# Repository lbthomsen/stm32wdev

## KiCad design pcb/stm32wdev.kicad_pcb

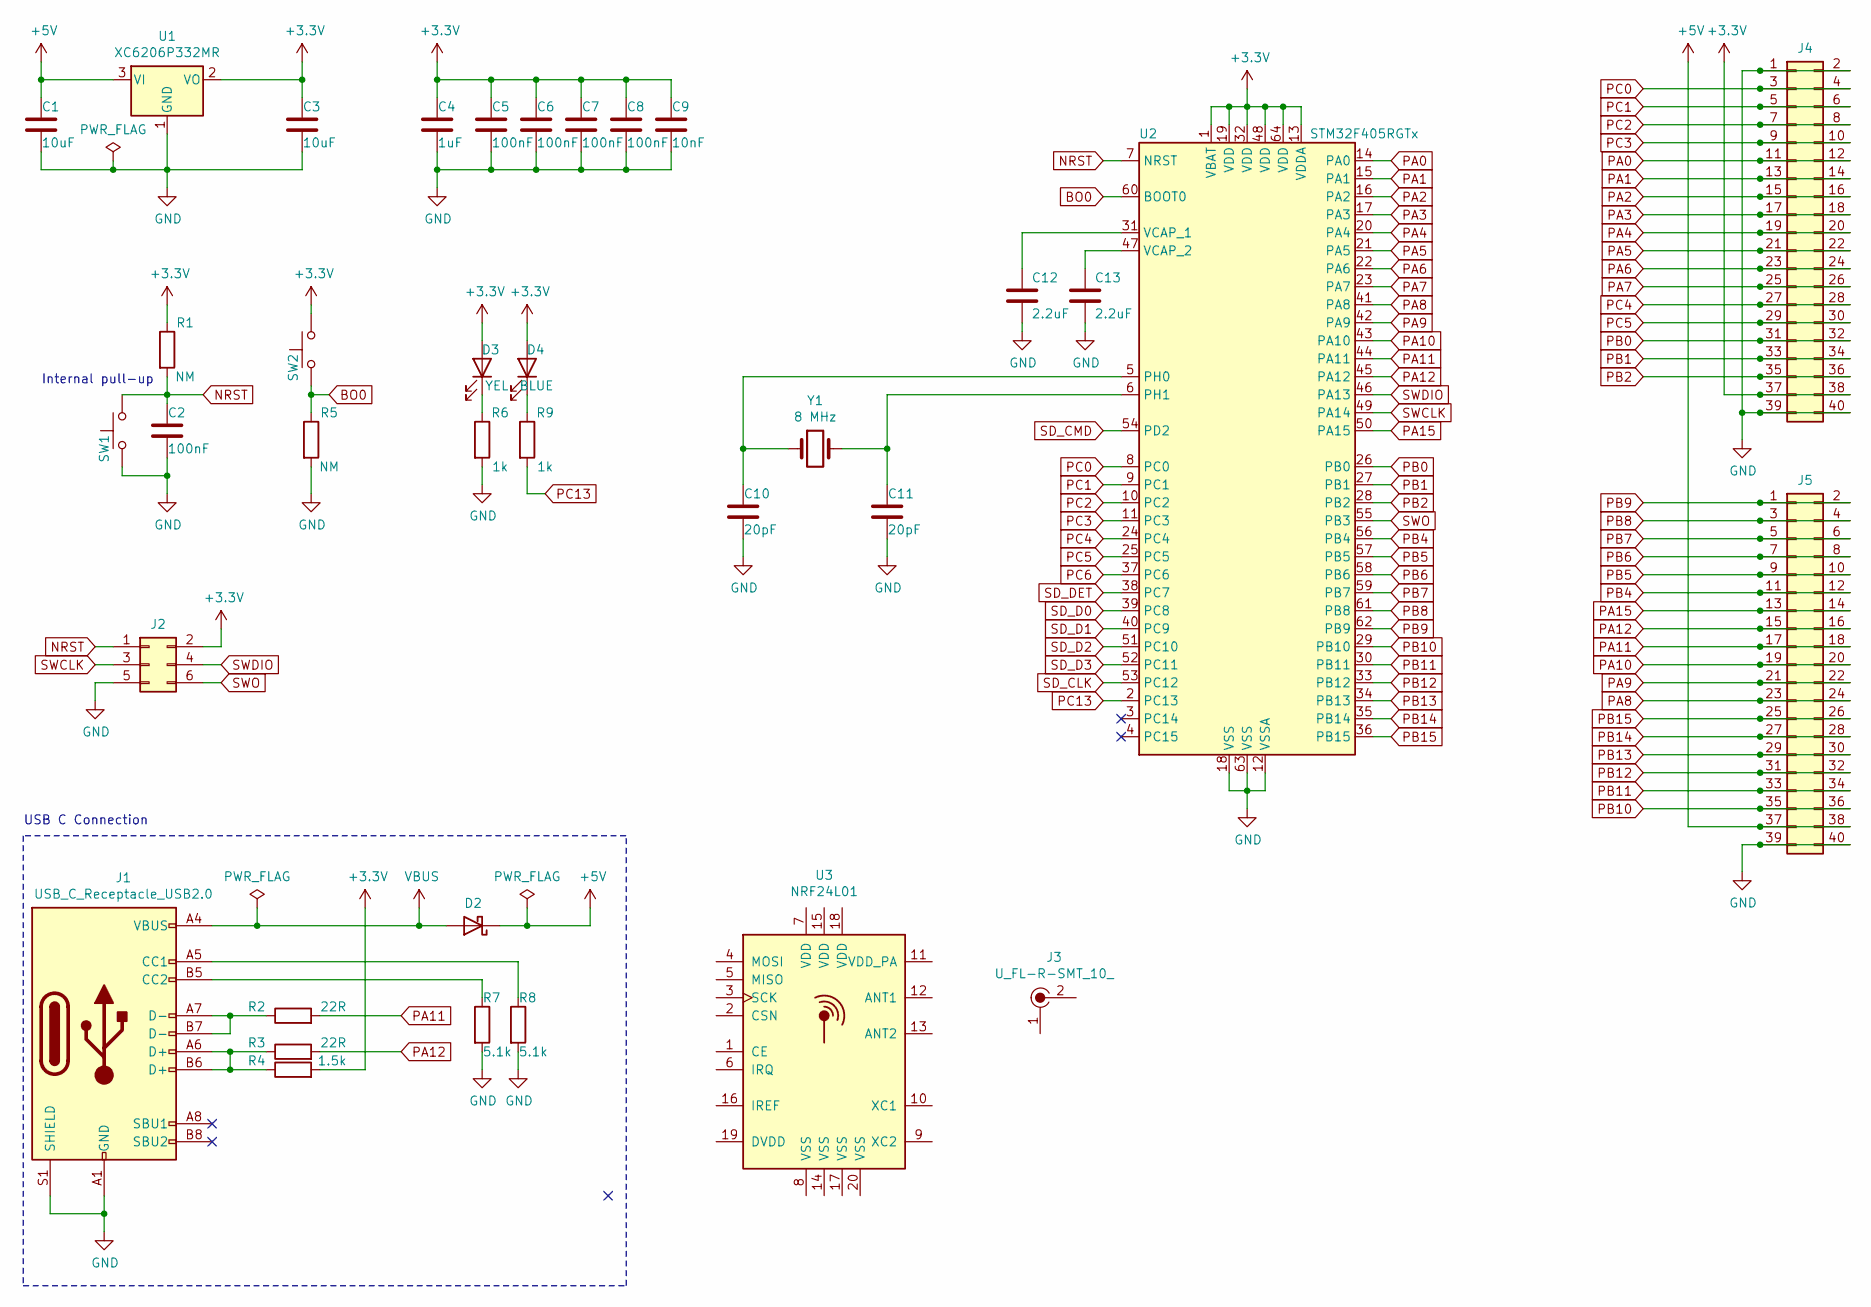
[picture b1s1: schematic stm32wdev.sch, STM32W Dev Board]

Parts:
C1, C3: 10uF; C_0805_2012Metric; LCSC C15850
C2, C5, C6, C7, C8: 100nF; C_0402_1005Metric; LCSC C1525
C4: 1uF; C_0402_1005Metric; LCSC C52923
C9: 10nF; C_0402_1005Metric; LCSC C15195
C10, C11: 20pF; C_0402_1005Metric; LCSC C1554
C12, C13: 2.2uF; C_0603_1608Metric; LCSC C23630
D2: D_SOD-123; LCSC C8598
D3: YEL; LED_0603_1608Metric; LCSC C72038
D4: BLUE; LED_0603_1608Metric; LCSC C72041
J1: USB_C_Receptacle_USB2.0; USB_C_Receptacle_HRO_TYPE-C-31-M-12; LCSC C167321
J2: PinHeader_2x03_P2.54mm_Horizontal
J3: U_FL-R-SMT_10_; Coax_Conn_U.FL; MPN U.FL-R-SMT(10); Digi-Key_PN H9161CT-ND
J4, J5: PinHeader_2x20_P2.54mm_Vertical
R1, R5: NM; R_0402_1005Metric
R2, R3: 22R; R_0402_1005Metric; LCSC C25092
R4: 1.5k; R_0402_1005Metric; LCSC C25867
R6, R9: 1k; R_0402_1005Metric; LCSC C25905
R7, R8: 5.1k; R_0402_1005Metric; LCSC C25905
SW1, SW2: SW_SPST_TL3342; LCSC C318887
U1: XC6206P332MR; SOT-23; LCSC C5446
U2: STM32F405RGTx; LQFP-64_10x10mm_P0.5mm; LCSC C15742
U3: NRF24L01; QFN-20-1EP_4x4mm_P0.5mm_EP2.5x2.5mm
Y1: 8 MHz; Crystal_SMD_Abracon_ABM3-2Pin_5.0x3.2mm; LCSC C115962

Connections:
+3V3: C3.1, C4.1, C5.1, C6.1, C7.1, C8.1, C9.1, D3.2 (A), D4.2 (A), J2.2, J4.37, J4.38, R1.1, R4.2, SW2.2, U1.2 (VO), U2.1 (VBAT), U2.13 (VDDA), U2.19 (VDD), U2.32 (VDD), U2.48 (VDD), U2.64 (VDD)
+5V: C1.1, D2.1 (K), J5.37, J5.38, U1.3 (VI)
BO0: R5.1, SW2.1, U2.60 (BOOT0)
GND: C1.2, C2.2, C3.2, C4.2, C5.2, C6.2, C7.2, C8.2, C9.2, C10.2, C11.2, C12.2, C13.2, J1.A1 (GND), J1.A12 (GND), J1.B1 (GND), J1.B12 (GND), J1.S1 (SHIELD), J2.5, J4.1, J4.2, J4.39, J4.40, J5.39, J5.40, R5.2, R6.2, R7.2, R8.2, SW1.1, U1.1 (GND), U2.12 (VSSA), U2.18 (VSS), U2.63 (VSS)
NRST: C2.1, J2.1, R1.2, SW1.2, U2.7 (NRST)
unnamed: C10.1, U2.5 (PH0), Y1.1
unnamed: C11.1, U2.6 (PH1), Y1.2
unnamed: C12.1, U2.31 (VCAP_1)
unnamed: C13.1, U2.47 (VCAP_2)
unnamed: D3.1 (K), R6.1
unnamed: D4.1 (K), R9.1
unnamed: J1.A5 (CC1), R8.1
unnamed: J1.A6 (D+), J1.B6 (D+), R3.1, R4.1
unnamed: J1.A7 (D-), J1.B7 (D-), R2.1
unnamed: J1.B5 (CC2), R7.1
PA0: J4.11, J4.12, U2.14 (PA0)
PA1: J4.13, J4.14, U2.15 (PA1)
PA2: J4.15, J4.16, U2.16 (PA2)
PA3: J4.17, J4.18, U2.17 (PA3)
PA4: J4.19, J4.20, U2.20 (PA4)
PA5: J4.21, J4.22, U2.21 (PA5)
PA6: J4.23, J4.24, U2.22 (PA6)
PA7: J4.25, J4.26, U2.23 (PA7)
PA8: J5.23, J5.24, U2.41 (PA8)
PA9: J5.21, J5.22, U2.42 (PA9)
PA10: J5.19, J5.20, U2.43 (PA10)
PA11: J5.17, J5.18, R2.2, U2.44 (PA11)
PA12: J5.15, J5.16, R3.2, U2.45 (PA12)
PA15: J5.13, J5.14, U2.50 (PA15)
PB0: J4.31, J4.32, U2.26 (PB0)
PB1: J4.33, J4.34, U2.27 (PB1)
PB2: J4.35, J4.36, U2.28 (PB2)
PB4: J5.11, J5.12, U2.56 (PB4)
PB5: J5.9, J5.10, U2.57 (PB5)
PB6: J5.7, J5.8, U2.58 (PB6)
PB7: J5.5, J5.6, U2.59 (PB7)
PB8: J5.3, J5.4, U2.61 (PB8)
PB9: J5.1, J5.2, U2.62 (PB9)
PB10: J5.35, J5.36, U2.29 (PB10)
PB11: J5.33, J5.34, U2.30 (PB11)
PB12: J5.31, J5.32, U2.33 (PB12)
PB13: J5.29, J5.30, U2.34 (PB13)
PB14: J5.27, J5.28, U2.35 (PB14)
PB15: J5.25, J5.26, U2.36 (PB15)
PC0: J4.3, J4.4, U2.8 (PC0)
PC1: J4.5, J4.6, U2.9 (PC1)
PC2: J4.7, J4.8, U2.10 (PC2)
PC3: J4.9, J4.10, U2.11 (PC3)
PC4: J4.27, J4.28, U2.24 (PC4)
PC5: J4.29, J4.30, U2.25 (PC5)
PC6: U2.37 (PC6)
PC13: R9.2, U2.2 (PC13)
SD_CLK: U2.53 (PC12)
SD_CMD: U2.54 (PD2)
SD_D0: U2.39 (PC8)
SD_D1: U2.40 (PC9)
SD_D2: U2.51 (PC10)
SD_D3: U2.52 (PC11)
SD_DET: U2.38 (PC7)
SWCLK: J2.3, U2.49 (PA14)
SWDIO: J2.4, U2.46 (PA13)
SWO: J2.6, U2.55 (PB3)
VBUS: D2.2 (A), J1.A4 (VBUS), J1.A9 (VBUS), J1.B4 (VBUS), J1.B9 (VBUS)

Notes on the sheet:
USB C Connection
Internal pull-up

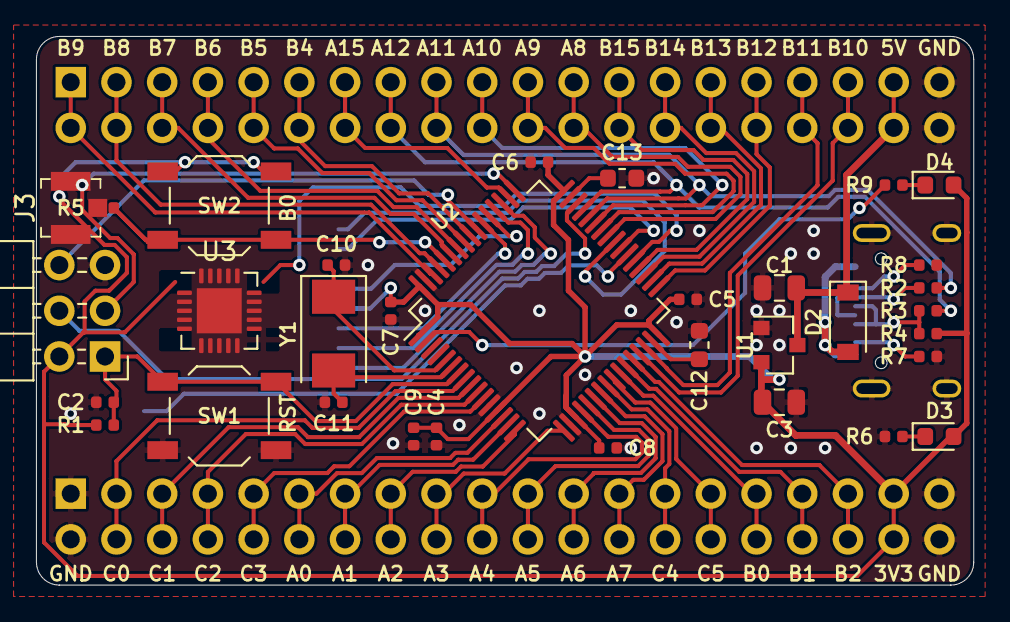
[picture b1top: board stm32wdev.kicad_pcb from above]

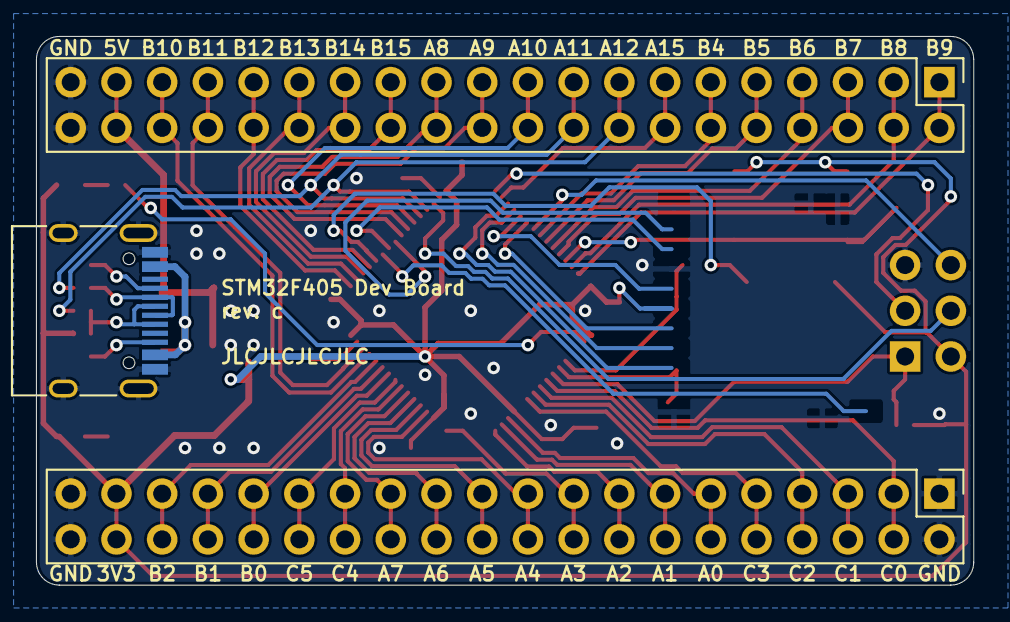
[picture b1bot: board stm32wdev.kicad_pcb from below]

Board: 2 copper layers, 52.1 x 30.5 mm, 36 parts (3 on the bottom side), 55 nets.

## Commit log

2020-11-12 Hmmm
